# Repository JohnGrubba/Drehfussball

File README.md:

# TourneyMaster - Drehfußballtisch-Tore-Zähler

### ESP32-gesteuerter Drehfußball-Tisch mit automatischer Torerkennung, LED-Anzeige
und Web-Turnierdashboard.

## Schnellstart

### Dashboard lokal / TV

```bash
cd dashboard
python3 -m pip install -r requirements.txt
python3 server.py
```

- **Live / Operator:** <http://localhost:8000/>
- **TV-/Turnieransicht:** <http://localhost:8000/tv> (oder `?tv=1`)
- **Demo-Turnier:** <http://localhost:8000/?demo=1&tv=1>
- **Gruppenphase:** zufälliger, ausbalancierter Spielplan mit Spieltagen und
  rotierenden Freilosen („Spielplan mischen“ vor dem ersten Spiel).
- **Spielerprofile:** jeder Spieler bekommt ein Profil im Browser-Speicher;
  Übersicht mit Platzierungen, Toren, Tordifferenz, Ø Toren und Turnierhistorie.
- **Teams für 2 gegen 2:** beim Anlegen 1–2 Spieler zu einem Turnier-Team
  gruppieren. Teams brauchen keinen Namen und werden automatisch als
  „Alice & Bob“ angezeigt.
- **Spielerauswahl:** beim Tippen erscheinen Vorschläge, ein Klick legt den
  Spieler in den Team-Slot; neue Namen werden direkt als Profil angelegt.
- **Teams übernehmen:** aus einem bestehenden Turnier alle oder die Top N Teams
  inklusive Gruppierung ins neue Turnier übernehmen.

Details: [dashboard/README.md](dashboard/README.md)

### Firmware

```bash
pio run -t upload
```

- Firmware: `src/` (Einstieg: `src/main.cpp`)
- Nach Dashboard-Änderungen: `python3 dashboard/build_site.py` (schreibt
  `src/site.cpp`), dann flashen.
- Partition: `huge_app.csv` (3 MB App, 1 MB SPIFFS), weil die Firmware inkl.
  Dashboard ca. 1,46 MB groß ist.
- Tor 1: J6 / S1 → GPIO27, Tor 2: J8 / S3 → GPIO32. Die 74HC14 invertieren:
  Strahl blockiert = GPIO HIGH. J7/J9 sind Reserve.

### Platine

- Fertigungspaket: `hardware/Drehfussball_Controller_Gerber.zip`
- Pinbelegung, BOM, Bestückung: [hardware/README.md](hardware/README.md)
- KiCad: `hardware/Drehfussball_Controller.kicad_pcb`
- DRC: 0 Verstöße, 0 unverbundene Pads.

## Struktur

| Pfad | Inhalt |
|---|---|
| `src/main.cpp` | Firmware-Einstieg (`setup()` / `loop()`) |
| `src/config.h` | Pins, Wi-Fi-Zugang, Zeit- und Debug-Konstanten |
| `src/game_state.*` | Spielstand sowie Tor-/Reset-Events zwischen Tasks |
| `src/sensors.*` | IR-Lichtschranken, ISR-Queue und Tor-Lockout |
| `src/leds.*` | LED-Spielstandsanzeige und Animationen |
| `src/stepper.*` | Ballrückgabe über den Schrittmotor |
| `src/webserver.*` | WLAN-Access-Point, HTTP- und WebSocket-Server |
| `src/site.cpp` | Generiertes Dashboard-HTML für den ESP32 |
| `dashboard/` | Dashboard-Quelle, lokaler Server, Screenshots |
| `hardware/` | KiCad-PCB, Gerber, BOM, Hardware-Doku |

## Hinweis

Der lokale `dashboard/server.py` simuliert den ESP32-WebSocket nur. Auf dem
ESP32 selbst läuft dieselbe Oberfläche unter `http://192.168.4.1/` (AP-Modus)
bzw. `http://192.168.4.1/?tv=1` für die TV-Ansicht.

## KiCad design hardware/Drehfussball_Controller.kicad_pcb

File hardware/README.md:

# Drehfussball Controller v1.0 — Platine

Trägerplatine für den automatischen Drehfußball-Tisch:

- ESP32-DevKitC V4 (38-Pin, **WROOM-32**, kein WROVER)
- A4988- / DRV8825-Schrittmotortreiber (2×8-Sockel)
- 2× IR-Lichtschranke (eine pro Schacht); 4 Eingänge auf der Platine (2 Reserve), 74HC14-Schmitt-Trigger
- 2× WS2812B-Streifen (5 V, 74AHCT125-Pegelwandler)
- Reset-Taster
- 12–24-V-Eingang mit 3-A-Sicherung, Verpolschutz, TVS und 5-V/2-A-Schaltregler

## Technische Daten

| Eigenschaft | Wert |
|---|---|
| Maße | 110 × 100 mm |
| Lagen | 2 (F.Cu / B.Cu) |
| Material | FR4, 1,6 mm, HASL |
| Bestückung | THT (keine SMD-Bauteile) |
| Min. Leiterbahn | 0,20 mm (geroutet: 0,20–0,40 mm, überwiegend 0,40 mm) |
| Min. Freiraum | 0,20 mm |
| Min. Bohrdurchmesser | 0,30 mm (Vias), 0,80 mm (DIP) |
| DRC (KiCad 9.0.2) | **0 Verstöße, 0 unverbundene Pads** |
| Routing | FreeRouting, überwiegend 0,40-mm-Tracks, B.Cu-GND-Fläche |
| Montage | 4× M3 (3,2 mm) |

## Stromversorgung

| Anschluss | Belegung |
|---|---|
| **J1** 12–24 V IN | 1 = +12…24 V, 2 = GND |
| **F1** | 5×20 mm, 3 A träge |
| **D1** | SR560, Verpolschutz (Kathode Richtung VIN_PROT) |
| **D2** | P6KE33A, TVS |
| **U1** | TSR2-2450, 5 V / 2 A (TO-220 SIP-3: 1 = IN, 2 = GND, 3 = OUT) |
| **JP1** | 1 = 5V_BUCK, 2 = +5 V, 3 = 5V_EXT; **1–2 = interner Regler**, 2–3 = externes 5 V |
| **J2** | 1 = 5V_EXT, 2 = GND |
| **JP2** | 1 = 3,3 V, 2 = SENSOR_VCC, 3 = 5 V; **1–2 = 3,3-V-Sensoren (Default)**, 2–3 = 5-V-Sensoren |

**Wichtig:** Niemals JP1 auf 2–3 stecken und gleichzeitig eine externe 5-V-Quelle an J2 anlegen, während der interne Regler bestückt ist. Im Zweifel JP1 abziehen.

Die 3,3 V kommen aus dem ESP32-DevKitC (AMS1117). Die Sensor-Pull-ups liegen immer an 3,3 V, auch wenn JP2 auf 5 V steht — dadurch sind 5-V-Open-Collector-Sensoren sicher.

**Stromreserve:** 5 V / 2 A. Das ESP32-Modul zieht ca. 0,5 A, die Sensorik ca. 0,1 A, der A4988-Logikteil ca. 0,05 A. Die Firmware begrenzt die LED-Streifen auf 500 mA. Für beide Streifen in voller Helligkeit (20 × 60 mA = 1,2 A) reicht der Regler gerade; besser ein separates 5-V-Netzteil für die LEDs verwenden und GND verbinden.

## Anschlüsse

### ESP32-DevKitC (J12 = J2-Header, J13 = J3-Header)

| J12 | Funktion | J13 | Funktion |
|---|---|---|---|
| 1 | 3V3 | 1 | GND |
| 2 | EN | 2 | IO23 |
| 3 | VP / IO36 | 3 | IO22 |
| 4 | VN / IO39 | 4 | TX / IO1 |
| 5 | IO34 | 5 | RX / IO3 |
| 6 | IO35 | 6 | **IO21 → DIR** |
| 7 | **IO32 → S3 (Tor 2)** | 7 | GND |
| 8 | **IO33 → BTN** | 8 | IO19 |
| 9 | **IO25 → LED_RED_DIN** | 9 | IO18 |
| 10 | **IO26 → LED_BLUE_DIN** | 10 | IO5 |
| 11 | **IO27 → S1 (Tor 1)** | 11 | **IO17 → EN** |
| 12 | IO14 → S2 (Reserve) | 12 | **IO16 → STEP** |
| 13 | IO12 (nicht verwendet!) | 13 | IO4 |
| 14 | GND | 14 | IO0 |
| 15 | IO13 → S4 (Reserve) | 15 | IO2 |
| 16 | D2 / IO9 | 16 | IO15 |
| 17 | D3 / IO10 | 17 | D1 / IO8 |
| 18 | CMD / IO11 | 18 | D0 / IO7 |
| 19 | 5V | 19 | CLK / IO6 |

**GPIO12 ist absichtlich frei.** Es ist ein Strapping-Pin (MTDI); ein Pull-up am Sensorausgang würde den ESP32 beim Booten auf 1,8 V Flash-Spannung stellen. Deshalb liegt Tor 2 auf **GPIO32**.

**Nur WROOM-32 verwenden.** Beim WROVER sind GPIO16/17 für PSRAM reserviert — STEP/EN würden nicht funktionieren.

### A4988 / DRV8825 (J3 = obere Reihe, J4 = untere Reihe)

| J3 | Funktion | J4 | Funktion |
|---|---|---|---|
| 1 | EN (GPIO17) | 1 | VMOT (12–24 V) |
| 2 | MS1 (JP3) | 2 | GND |
| 3 | MS2 (JP4) | 3 | 2B |
| 4 | MS3 (JP5) | 4 | 2A |
| 5 | RST (+5 V) | 5 | 1A |
| 6 | SLP (+5 V) | 6 | 1B |
| 7 | STEP (GPIO16) | 7 | VDD (+5 V) |
| 8 | DIR (GPIO21) | 8 | GND |

- **RST und SLP sind auf der Platine fest mit +5 V verbunden.**
- **JP3/JP4/JP5** schalten MS1/MS2/MS3 auf +5 V. Offen = Low (interne Pulldowns im A4988).
- A4988: alle drei geschlossen = 1/16. DRV8825: alle drei geschlossen = 1/32.
- **J5 MOTOR:** 1 = 1A, 2 = 1B, 3 = 2A, 4 = 2B.
- Modul mit Pin 1 (EN) an J3 Pin 1 einstecken; Trimpot nach oben. **Stromgrenze vor dem Anschließen des Motors einstellen.**

### Lichtschranken (J6 / J8)

Der Ball läuft im geschlossenen Schacht an der Lichtschranke vorbei. Eine Schranke pro Seite reicht; niemand kann in den Schacht greifen, deshalb ist keine Doppelstrahl- oder Hand-Erkennung nötig.

| Anschluss | Tor | GPIO | Status |
|---|---|---|---|
| J6 / S1 | Tor 1 (blau) | 27 | **verwendet** |
| J8 / S3 | Tor 2 (rot) | 32 | **verwendet** |
| J7 / S2 | Reserve | 14 | optional |
| J9 / S4 | Reserve | 13 | optional |

Belegung: **1 = VCC (JP2), 2 = OUT, 3 = GND**.

- Die 74HC14 **invertieren**: Strahl unterbrochen → **GPIO HIGH**.
- 10 kΩ Pull-up auf 3,3 V, 1 kΩ Serienwiderstand, 100 nF gegen GND.
- **Sender:** Der 3-polige Header versorgt den Empfänger. Der IR-Sender (2-polig) wird parallel an VCC/GND angeschlossen; Vorwiderstand passend zur LED (bei 3,3 V ca. 100 Ω, bei 5 V ca. 180 Ω für 20 mA). Bei fertigen 3-Draht-Modulen mit integriertem Sender entfällt das.
- Die Platine ist für **3,3–5-V-Open-Collector-Module** ausgelegt. Für 12–24-V-Industriesensoren wäre ein Optokoppler nötig (nicht auf dieser Version).

**Bestückung der Reserve-Kanäle:** R2–R9 und C6–C9 trotzdem vollständig bestücken, auch wenn J7/J9 leer bleiben. Sonst können die ungenutzten 74HC14-Eingänge floaten. Die Buchsen J7/J9 selbst sind optional.

### LEDs (J10/J11)

| Anschluss | Belegung |
|---|---|
| J10 LED BLUE | 1 = 5 V, 2 = DIN (GPIO26 über U3), 3 = GND |
| J11 LED RED | 1 = 5 V, 2 = DIN (GPIO25 über U3), 3 = GND |

- 74AHCT125 wandelt 3,3 V auf 5 V; 330 Ω Serienwiderstand; 1000 µF Stützkondensator.
- WS2812B, 10 LEDs pro Streifen (wie in der Firmware).

## Bestückung

### BOM (Platine)

Die vollständige, gruppierte Liste steht in [`BOM_grouped.csv`](BOM_grouped.csv); die Einzelpositionen in [`BOM.csv`](BOM.csv).

| Menge | Wert | Referenzen |
|---:|---|---|
| 11 | 100 nF | C2, C4–C13 |
| 1 | 470 µF / 50 V | C1 |
| 1 | 470 µF / 10 V | C3 |
| 1 | 100 µF / 50 V | C14 |
| 1 | 1000 µF / 10 V | C15 |
| 5 | 10 kΩ | R2–R5, R10 |
| 5 | 1 kΩ | R1, R6–R9 |
| 2 | 330 Ω | R14, R15 |
| 1 | SR560 | D1 |
| 1 | P6KE33A | D2 |
| 1 | LED grün 5 mm | LED1 |
| 1 | TSR2-2450 | U1 |
| 1 | 74HC14 (DIP-14) | U2 |
| 1 | 74AHCT125 (DIP-14) | U3 |
| 1 | Taster 6 mm | SW1 |
| 1 | 5×20-mm-Sicherungshalter | F1 |
| 2 | 1×19-Pin-Socket | J12, J13 |
| 2 | 1×8-Pin-Socket | J3, J4 |
| 4 | 1×3-Pin-Socket | J6–J9 (2 genutzt, 2 Reserve) |
| 1 | 2-Pin-Schraubklemme 5,08 mm | J1 |
| 3 | 3,5-mm-Schraubklemme, 3/3/4-polig | J10, J11, J5 |
| 4 | 1×2-Stiftleiste | J2, JP3, JP4, JP5 |
| 2 | 1×3-Stiftleiste | JP1, JP2 |
| 4 | M3-Bohrung | H1–H4 |

### Externe Teile (nicht auf der Platine)

- ESP32-DevKitC V4, 38-Pin, **ESP32-WROOM-32E**
- A4988- oder DRV8825-Modul, 2×8, 0,6″
- 2× IR-Lichtschrankenpaar (eine pro Schacht, Sender + Empfänger, 3,3–5 V, Open Collector)
- 1× Feinsicherung 5×20 mm, 3 A träge
- 2× WS2812B-Streifen, 5 V, 10 LEDs
- 12–24-V-DC-Netzteil (mind. 2 A für den Motor; 5-V-Zweig max. 2 A)
- Schrittmotor, 4-adrig
- Jumper-Kappen für JP1–JP5
- Optional: Kühlkörper für U1 bei >1 A Dauerstrom

### Bestückungsreihenfolge

1. Widerstände und Dioden (R1–R15, D1, D2)
2. Keramik- und Elko-Kondensatoren (auf Polarität achten: C1, C3, C14, C15)
3. DIP-14-Sockel für U2/U3, dann ICs einsetzen
4. Taster SW1, LED1
5. Sicherungshalter F1, Schraubklemmen J1/J5/J10/J11
6. Stiftleisten JP1–JP5, J2
7. Buchsenleisten J3/J4, J6/J8 (J7/J9 Reserve), J12/J13
8. U1 (TO-220) zuletzt, ggf. Kühlkörper

**Polarität:**
- D1: Kathodenband (K) nach rechts zu VIN_PROT.
- D2: Kathodenband (K) nach links zu VIN_PROT.
- C1/C3/C14/C15: „+“-Markierung beachten (quadratisches Pad = Plus).
- LED1: Kathode (flache Seite) an GND.

**Antennen-Keepout:** Der linke Bereich (x = 0…11 mm, y = 33…70 mm) ist auf beiden Lagen copper-free. Dort darf kein Metall und kein Kabel liegen; die ESP32-Antenne zeigt nach links.

## Firmware

`src/main.cpp` ist bereits auf die Platine umgestellt:

- **Tor 1** (blau): `J6 / S1` → **GPIO27**
- **Tor 2** (rot): `J8 / S3` → **GPIO32**
- `J7 / S2` und `J9 / S4` bleiben frei.
- **74HC14 invertiert:** Strahl blockiert = `HIGH`.
- Der Taster bleibt **active-low** auf GPIO33 (nicht über den Inverter geführt).
- `STEP`/`DIR`/`EN` bleiben auf 16/21/17; die LED-Pins bleiben 26/25.

Die alte `pulseIn`/`SensorLoop`-Logik und `RunningMedian` sind entfernt. Stattdessen:

1. `attachInterrupt(..., CHANGE)` auf GPIO27 und GPIO32.
2. Die ISR trägt nur `(Tor, Flanke, Zeitstempel)` in eine FreeRTOS-Queue ein.
3. Ein Task wertet die Queue aus:
   - Blockierdauer **2–500 ms** → Tor.
   - **< 2 ms** → Störung/Schmutz, kein Tor.
   - **> 500 ms** → klemmender Ball oder Sensorfehler, kein Tor.
   - **1,5 s Cooldown** pro Seite gegen Doppelzählung.

Damit wird nicht mehr periodisch gemessen; die CPU reagiert nur auf Flanken. Zum Debuggen `DEBUG_SENSORS` in `src/main.cpp` auf `1` setzen.

### Firmware-Build

Getestet mit PlatformIO 6.x, Arduino Core 3.x (ESP-IDF 5.5) und **FastAccelStepper 2.0.0**. Die Firmware ist inkl. Dashboard ca. 1,4 MB groß; deshalb steht in `platformio.ini`:

```ini
board_build.partitions = huge_app.csv
```

Das gibt eine 3-MB-App-Partition (statt 1,25 MB) und 1 MB SPIFFS. Ohne diese Zeile schlägt der Linker mit „program size is greater than maximum allowed“ fehl.

```bash
pio run                 # kompilieren
pio run -t upload       # flashen
```

### Dashboard lokal / TV

Das Web-Dashboard liegt unter [`../dashboard/`](../dashboard/) und ist dieselbe
Oberfläche, die der ESP32 ausliefert.

```bash
cd dashboard
python3 -m pip install -r requirements.txt
python3 server.py
```

- **Live / Operator:** <http://localhost:8000/>
- **TV:** <http://localhost:8000/tv> (oder `?tv=1`)
- **Demo:** <http://localhost:8000/?demo=1&tv=1>

Auf dem ESP32: `http://192.168.4.1/` bzw. `http://192.168.4.1/?tv=1`
(oder `/tv`). Der lokale Server simuliert den WebSocket nur; die echte
Firmware läuft auf dem ESP32.

Nach Dashboard-Änderungen `python3 dashboard/build_site.py` ausführen (macht
`server.py` beim Start automatisch) und anschließend `pio run -t upload`.

Details: [`../dashboard/README.md`](../dashboard/README.md)

## Build (optional)

Die Platine lässt sich mit den Skripten in diesem Ordner reproduzieren. Benötigt werden KiCad 9 (`kicad-cli`, `pcbnew`), Java 25 und FreeRouting 2.5. Für den Schaltplan zusätzlich `kicad-sch-api` (pip) und `KICAD_SYMBOL_DIR`. Die Pfade lassen sich über die Umgebungsvariablen `JAVA`, `FREEROUTING` und `KICAD_CLI` überschreiben.

```bash
export LD_LIBRARY_PATH=/pfad/zu/kicad/usr/lib/x86_64-linux-gnu
export PYTHONPATH=/pfad/zu/kicad/usr/lib/python3/dist-packages
python3 build.py            # Platzierung, Routing, DRC, Gerber
python3 generate_schematic.py
python3 generate_docs.py
```

## Fertigung

- Gerber + Bohrdaten: [`Drehfussball_Controller_Gerber.zip`](Drehfussball_Controller_Gerber.zip)
- Enthalten: F.Cu, B.Cu, F/B-Maske, F/B-Silkscreen, Edge.Cuts, PTH/NPTH-Drill, `.gbrjob`
- 2 Lagen, 1,6 mm, HASL, min. Track 0,2 mm, min. Drill 0,3 mm
- Bei JLCPCB/PCBWay/Aisler direkt als ZIP hochladen; 5 Stück sind ausreichend.

## Dateien

| Datei | Inhalt |
|---|---|
| `Drehfussball_Controller.kicad_pcb` | KiCad-9-PCB, geroutet |
| `Drehfussball_Controller.kicad_pro` | Projektdatei (DRC-Regeln) |
| `Drehfussball_Controller.kicad_sch` | KiCad-9-Schaltplan (Netzlabels) |
| `Drehfussball_Controller_Schematic.pdf` | Schaltplan als PDF |
| `BOM.csv` / `BOM_grouped.csv` | Stücklisten |
| `connections.csv` | Netz → Bauteil/Pad |
| `gerber/` | Einzelne Gerber- und Bohrdaten |
| `Drehfussball_Controller_Gerber.zip` | Fertigungspaket |
| `final_top.png` / `final_all.png` | Vorschau Top / beide Lagen |
| `schematic.png` | Vorschau Schaltplan |
| `generate_board.py` | Erzeugt Platzierung + Netze |
| `build.py` | Kompletter Build: Route, DRC, Gerber |
| `generate_schematic.py` | Erzeugt den KiCad-Schaltplan |
| `generate_docs.py` | Erzeugt BOM- und Verbindungstabellen |
| `../src/main.cpp` | Firmware: IR-Auswertung, LEDs, Stepper, WebSocket |
| `../platformio.ini` | PlatformIO: FastAccelStepper 2.0.0, huge_app-Partition |
| `../dashboard/` | Dashboard-Quelle, lokaler Mock-Server, TV-Ansicht |

## Bekannte Einschränkungen

- Der Schaltplan ist **automatisch** aus denselben Netzen erzeugt und nutzt Netzlabels an jedem Pin. Er ist elektrisch konsistent, aber optisch dicht; für eine „schöne“ Zeichnung in KiCad öffnen und aufräumen.
- Der Schaltplan zeigt alle vier Sensor-Kanäle. Genutzt werden **S1 (J6)** und **S3 (J8)**; S2/S4 sind Reserve.
- Die 5-V-Leiterbahnen sind 0,3–0,4 mm. Für >1,5 A Dauerstrom besser ein separates 5-V-Kabel an J10/J11 führen oder die Bahnen verbreitern.
- Die IR-Sensoren sind extern; die Platine erwartet 3,3–5-V-Open-Collector-Module. 12–24-V-Industriesensoren brauchen einen Optokoppler.
- Das A4988-Modul, der ESP32, die LED-Streifen, der Motor und das Netzteil sind **nicht** Teil der Platine.
- Die DRC-Prüfung ignoriert reine Silk-/Courtyard-Überlappungen (kosmetisch). Elektrische Prüfungen (Kurzschluss, Freiraum, unverbundene Pads) sind aktiv und sauber.

## Lizenz / Haftung

Prototypen-Design. Vor der Fertigung die Gerber im Viewer prüfen und die Bestückung gegen die eigene Mechanik kontrollieren. Keine Gewähr für Richtigkeit der Pinbelegung oder für Schäden an ESP32, Treiber, Motor oder Netzteil.

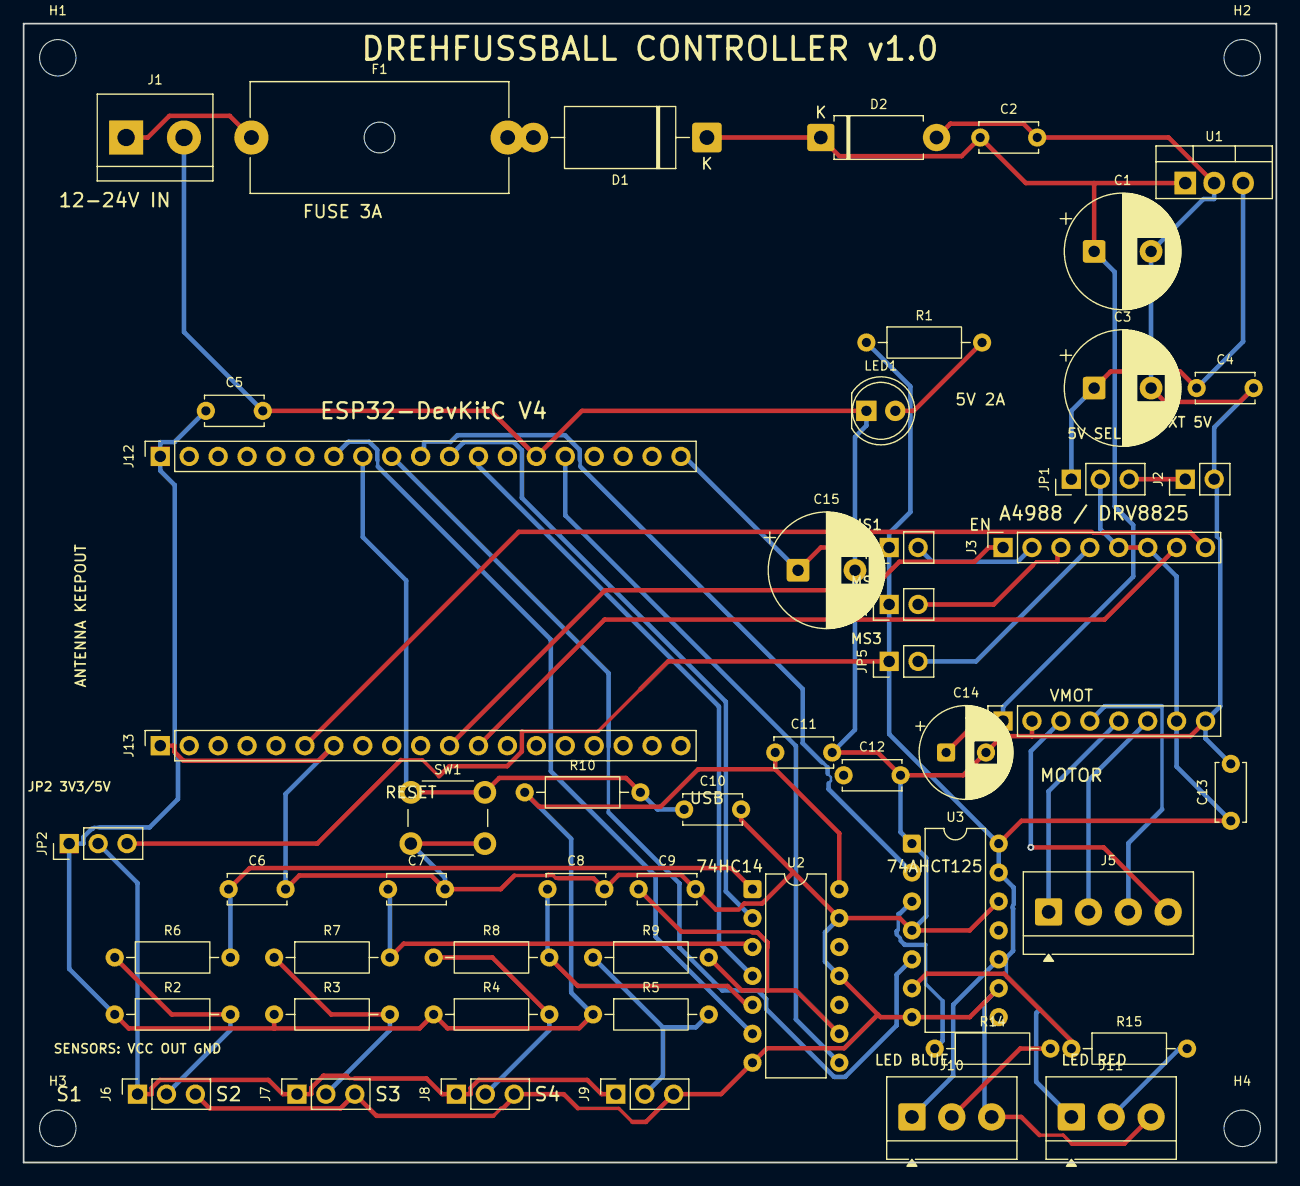
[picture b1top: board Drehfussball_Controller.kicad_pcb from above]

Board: 2 copper layers, 110.0 x 100.0 mm, 57 parts (0 on the bottom side), 39 nets.

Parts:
C1: 470uF/50V; CP_Radial_D10.0mm_P5.00mm
C2, C4, C5, C6, C7, C8, C9, C10, C11, C12, C13: 100nF; C_Disc_D5.0mm_W2.5mm_P5.00mm
C3: 470uF/10V; CP_Radial_D10.0mm_P5.00mm
C14: 100uF/50V; CP_Radial_D8.0mm_P3.50mm
C15: 1000uF/10V; CP_Radial_D10.0mm_P5.00mm
D1: SR560; D_DO-201_P15.24mm_Horizontal
D2: P6KE33A; D_DO-15_P10.16mm_Horizontal
F1: FUSE 5x20 3A; Fuseholder_Cylinder-5x20mm_Schurter_0031_8201_Horizontal_Op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
H1, H2, H3, H4: M3; MountingHole_3.2mm_M3
J1: 12-24V IN; TerminalBlock_bornier-2_P5.08mm
J2: 5V EXT; PinHeader_1x02_P2.54mm_Vertical
J3: A4988 TOP; PinSocket_1x08_P2.54mm_Vertical
J4: A4988 BOT; PinSocket_1x08_P2.54mm_Vertical
J5: MOTOR; TerminalBlock_4Ucon_1x04_P3.50mm_Horizontal
J6: S1; PinSocket_1x03_P2.54mm_Vertical
J7: S2; PinSocket_1x03_P2.54mm_Vertical
J8: S3; PinSocket_1x03_P2.54mm_Vertical
J9: S4; PinSocket_1x03_P2.54mm_Vertical
J10: LED BLUE; TerminalBlock_4Ucon_1x03_P3.50mm_Horizontal
J11: LED RED; TerminalBlock_4Ucon_1x03_P3.50mm_Horizontal
J12: ESP32 J2; PinSocket_1x19_P2.54mm_Vertical
J13: ESP32 J3; PinSocket_1x19_P2.54mm_Vertical
JP1: 5V SEL; PinHeader_1x03_P2.54mm_Vertical
JP2: SENSOR VCC; PinHeader_1x03_P2.54mm_Vertical
JP3: MS1; PinHeader_1x02_P2.54mm_Vertical
JP4: MS2; PinHeader_1x02_P2.54mm_Vertical
JP5: MS3; PinHeader_1x02_P2.54mm_Vertical
LED1: GREEN; LED_D5.0mm
R1, R6, R7, R8, R9: 1k; R_Axial_DIN0207_L6.3mm_D2.5mm_P10.16mm_Horizontal
R2, R3, R4, R5, R10: 10k; R_Axial_DIN0207_L6.3mm_D2.5mm_P10.16mm_Horizontal
R14, R15: 330R; R_Axial_DIN0207_L6.3mm_D2.5mm_P10.16mm_Horizontal
SW1: RESET; SW_PUSH_6mm
U1: TSR2-2450; TO-220-3_Vertical
U2: 74HC14; DIP-14_W7.62mm
U3: 74AHCT125; DIP-14_W7.62mm

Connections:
5V_BUCK: C3.1, C4.1, JP1.1, U1.3
5V_EXT: J2.1, JP1.3
+3V3: C5.1, C11.1, J12.1, JP2.1, R2.1, R3.1, R4.1, R5.1, R10.1, U2.14
+5V: C13.1, C15.1, J3.5, J3.6, J4.7, J10.1, J11.1, J12.19, JP1.2, JP2.3, JP3.1, JP4.1, JP5.1, R1.1, U3.10, U3.13, U3.14
BTN: C10.1, J12.8, R10.2, SW1.1
DIR: J3.8, J13.6
EN: J3.1, J13.11
GND: C1.2, C2.2, C3.2, C4.2, C5.2, C6.2, C7.2, C8.2, C9.2, C10.2, C11.2, C12.2, C13.2, C14.2, C15.2, D2.2, J1.2, J2.2, J4.2, J4.8, J6.3, J7.3, J8.3, J9.3, J10.3, J11.3, J12.14, J13.1, J13.7, LED1.1, SW1.2, U1.2, U2.7, U2.11, U2.13, U3.1, U3.4, U3.7, U3.9, U3.12
LED_A: LED1.2, R1.2
LED_BLUE: R14.1, U3.3
LED_BLUE_DIN: J12.10, U3.2
LED_BLUE_STRIP: J10.2, R14.2
LED_RED: R15.1, U3.6
LED_RED_DIN: J12.9, U3.5
LED_RED_STRIP: J11.2, R15.2
MOT_1A: J4.5, J5.1
MOT_1B: J4.6, J5.2
MOT_2A: J4.4, J5.3
MOT_2B: J4.3, J5.4
MS1: J3.2, JP3.2
MS2: J3.3, JP4.2
MS3: J3.4, JP5.2
S1_F: C6.1, R6.2, U2.1
S1_OUT: J12.11, U2.2
S1_RAW: J6.2, R2.2, R6.1
S2_F: C7.1, R7.2, U2.3
S2_OUT: J12.12, U2.4
S2_RAW: J7.2, R3.2, R7.1
S3_F: C8.1, R8.2, U2.5
S3_OUT: J12.7, U2.6
S3_RAW: J8.2, R4.2, R8.1
S4_F: C9.1, R9.2, U2.9
S4_OUT: J12.15, U2.8
S4_RAW: J9.2, R5.2, R9.1
SENSOR_VCC: J6.1, J7.1, J8.1, J9.1, JP2.2
STEP: J3.7, J13.12
VIN: F1.1, J1.1
VIN_F: D1.2, F1.2
VIN_PROT: C1.1, C2.1, C14.1, D1.1, D2.1, J4.1, U1.1

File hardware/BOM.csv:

Reference,Value,Footprint,Description,X_mm,Y_mm,Rotation
J1,12-24V IN,TerminalBlock.pretty/TerminalBlock_bornier-2_P5.08mm,Screw terminal 12-24 V input,9.00,10.00,0
F1,FUSE 5x20 3A,Fuse.pretty/Fuseholder_Cylinder-5x20mm_Schurter_0031_8201_Horizontal_Open,5x20 mm fuse holder,20.00,10.00,0
D1,SR560,Diode_THT.pretty/D_DO-201_P15.24mm_Horizontal,Reverse polarity protection,60.00,10.00,180
D2,P6KE33A,Diode_THT.pretty/D_DO-15_P10.16mm_Horizontal,TVS transient protection,70.00,10.00,0
C2,100nF,Capacitor_THT.pretty/C_Disc_D5.0mm_W2.5mm_P5.00mm,Input HF decoupling,84.00,10.00,0
C1,470uF/50V,Capacitor_THT.pretty/CP_Radial_D10.0mm_P5.00mm,Input bulk capacitor,94.00,20.00,0
U1,TSR2-2450,Package_TO_SOT_THT.pretty/TO-220-3_Vertical,5 V 2 A switching regulator,102.00,14.00,0
C3,470uF/10V,Capacitor_THT.pretty/CP_Radial_D10.0mm_P5.00mm,5 V bulk capacitor,94.00,32.00,0
C4,100nF,Capacitor_THT.pretty/C_Disc_D5.0mm_W2.5mm_P5.00mm,5 V HF decoupling,103.00,32.00,0
JP1,5V SEL,Connector_PinHeader_2.54mm.pretty/PinHeader_1x03_P2.54mm_Vertical,"5 V source select: 1-2 internal, 2-3 external",92.00,40.00,90
J2,5V EXT,Connector_PinHeader_2.54mm.pretty/PinHeader_1x02_P2.54mm_Vertical,External 5 V input,102.00,40.00,90
R1,1k,Resistor_THT.pretty/R_Axial_DIN0207_L6.3mm_D2.5mm_P10.16mm_Horizontal,Power LED resistor,74.00,28.00,0
LED1,GREEN,LED_THT.pretty/LED_D5.0mm,Power LED,74.00,34.00,0
J12,ESP32 J2,Connector_PinSocket_2.54mm.pretty/PinSocket_1x19_P2.54mm_Vertical,ESP32-DevKitC J2 socket,12.00,38.00,90
J13,ESP32 J3,Connector_PinSocket_2.54mm.pretty/PinSocket_1x19_P2.54mm_Vertical,ESP32-DevKitC J3 socket,12.00,63.40,90
C5,100nF,Capacitor_THT.pretty/C_Disc_D5.0mm_W2.5mm_P5.00mm,3V3 decoupling,16.00,34.00,0
J3,A4988 TOP,Connector_PinSocket_2.54mm.pretty/PinSocket_1x08_P2.54mm_Vertical,A4988/DRV8825 left row,86.00,46.00,90
J4,A4988 BOT,Connector_PinSocket_2.54mm.pretty/PinSocket_1x08_P2.54mm_Vertical,A4988/DRV8825 right row,86.00,61.24,90
C14,100uF/50V,Capacitor_THT.pretty/CP_Radial_D8.0mm_P3.50mm,Stepper VMOT bulk capacitor,81.00,64.00,0
C13,100nF,Capacitor_THT.pretty/C_Disc_D5.0mm_W2.5mm_P5.00mm,Stepper VDD decoupling,106.00,70.00,90
JP3,MS1,Connector_PinHeader_2.54mm.pretty/PinHeader_1x02_P2.54mm_Vertical,Microstep MS1 to +5 V,76.00,46.00,90
JP4,MS2,Connector_PinHeader_2.54mm.pretty/PinHeader_1x02_P2.54mm_Vertical,Microstep MS2 to +5 V,76.00,51.00,90
JP5,MS3,Connector_PinHeader_2.54mm.pretty/PinHeader_1x02_P2.54mm_Vertical,Microstep MS3 to +5 V,76.00,56.00,90
J5,MOTOR,TerminalBlock_4Ucon.pretty/TerminalBlock_4Ucon_1x04_P3.50mm_Horizontal,Stepper motor 1A 1B 2A 2B,90.00,78.00,0
U2,74HC14,Package_DIP.pretty/DIP-14_W7.62mm,"Schmitt trigger, inverting",64.00,76.00,0
J6,S1,Connector_PinSocket_2.54mm.pretty/PinSocket_1x03_P2.54mm_Vertical,Goal 1 beam A,10.00,94.00,90
J7,S2,Connector_PinSocket_2.54mm.pretty/PinSocket_1x03_P2.54mm_Vertical,Goal 1 beam B,24.00,94.00,90
J8,S3,Connector_PinSocket_2.54mm.pretty/PinSocket_1x03_P2.54mm_Vertical,Goal 2 beam A,38.00,94.00,90
J9,S4,Connector_PinSocket_2.54mm.pretty/PinSocket_1x03_P2.54mm_Vertical,Goal 2 beam B,52.00,94.00,90
R2,10k,Resistor_THT.pretty/R_Axial_DIN0207_L6.3mm_D2.5mm_P10.16mm_Horizontal,S1 pull-up,8.00,87.00,0
R3,10k,Resistor_THT.pretty/R_Axial_DIN0207_L6.3mm_D2.5mm_P10.16mm_Horizontal,S2 pull-up,22.00,87.00,0
R4,10k,Resistor_THT.pretty/R_Axial_DIN0207_L6.3mm_D2.5mm_P10.16mm_Horizontal,S3 pull-up,36.00,87.00,0
R5,10k,Resistor_THT.pretty/R_Axial_DIN0207_L6.3mm_D2.5mm_P10.16mm_Horizontal,S4 pull-up,50.00,87.00,0
R6,1k,Resistor_THT.pretty/R_Axial_DIN0207_L6.3mm_D2.5mm_P10.16mm_Horizontal,S1 series,8.00,82.00,0
R7,1k,Resistor_THT.pretty/R_Axial_DIN0207_L6.3mm_D2.5mm_P10.16mm_Horizontal,S2 series,22.00,82.00,0
R8,1k,Resistor_THT.pretty/R_Axial_DIN0207_L6.3mm_D2.5mm_P10.16mm_Horizontal,S3 series,36.00,82.00,0
R9,1k,Resistor_THT.pretty/R_Axial_DIN0207_L6.3mm_D2.5mm_P10.16mm_Horizontal,S4 series,50.00,82.00,0
C6,100nF,Capacitor_THT.pretty/C_Disc_D5.0mm_W2.5mm_P5.00mm,S1 filter,18.00,76.00,0
C7,100nF,Capacitor_THT.pretty/C_Disc_D5.0mm_W2.5mm_P5.00mm,S2 filter,32.00,76.00,0
C8,100nF,Capacitor_THT.pretty/C_Disc_D5.0mm_W2.5mm_P5.00mm,S3 filter,46.00,76.00,0
C9,100nF,Capacitor_THT.pretty/C_Disc_D5.0mm_W2.5mm_P5.00mm,S4 filter,54.00,76.00,0
C11,100nF,Capacitor_THT.pretty/C_Disc_D5.0mm_W2.5mm_P5.00mm,74HC14 decoupling,66.00,64.00,0
SW1,RESET,Button_Switch_THT.pretty/SW_PUSH_6mm,Reset button,34.00,67.50,0
R10,10k,Resistor_THT.pretty/R_Axial_DIN0207_L6.3mm_D2.5mm_P10.16mm_Horizontal,Reset pull-up,44.00,67.50,0
C10,100nF,Capacitor_THT.pretty/C_Disc_D5.0mm_W2.5mm_P5.00mm,Reset debounce,58.00,69.00,0
U3,74AHCT125,Package_DIP.pretty/DIP-14_W7.62mm,WS2812 level shifter,78.00,72.00,0
C12,100nF,Capacitor_THT.pretty/C_Disc_D5.0mm_W2.5mm_P5.00mm,74AHCT125 decoupling,72.00,66.00,0
R14,330R,Resistor_THT.pretty/R_Axial_DIN0207_L6.3mm_D2.5mm_P10.16mm_Horizontal,Blue LED data series,80.00,90.00,0
R15,330R,Resistor_THT.pretty/R_Axial_DIN0207_L6.3mm_D2.5mm_P10.16mm_Horizontal,Red LED data series,92.00,90.00,0
J10,LED BLUE,TerminalBlock_4Ucon.pretty/TerminalBlock_4Ucon_1x03_P3.50mm_Horizontal,WS2812 blue strip,78.00,96.00,0
J11,LED RED,TerminalBlock_4Ucon.pretty/TerminalBlock_4Ucon_1x03_P3.50mm_Horizontal,WS2812 red strip,92.00,96.00,0
C15,1000uF/10V,Capacitor_THT.pretty/CP_Radial_D10.0mm_P5.00mm,LED strip bulk capacitor,68.00,48.00,0
H1,M3,MountingHole.pretty/MountingHole_3.2mm_M3,Mounting hole,3.00,3.00,0
H2,M3,MountingHole.pretty/MountingHole_3.2mm_M3,Mounting hole,107.00,3.00,0
H3,M3,MountingHole.pretty/MountingHole_3.2mm_M3,Mounting hole,3.00,97.00,0
H4,M3,MountingHole.pretty/MountingHole_3.2mm_M3,Mounting hole,107.00,97.00,0
JP2,SENSOR VCC,Connector_PinHeader_2.54mm.pretty/PinHeader_1x03_P2.54mm_Vertical,"1-2 = 3V3, 2-3 = 5V",4.00,72.00,90

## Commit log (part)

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2026-05-04 UI Fixes Stability Issues fixed
2026-05-10 Add Stepper Motor
2026-05-10 Automatic Ball Dispensing
2026-06-13 Fixed Everything
2026-06-13 Ye idk
2026-06-13 Safer Mode
2026-06-20 Fix shutdown
